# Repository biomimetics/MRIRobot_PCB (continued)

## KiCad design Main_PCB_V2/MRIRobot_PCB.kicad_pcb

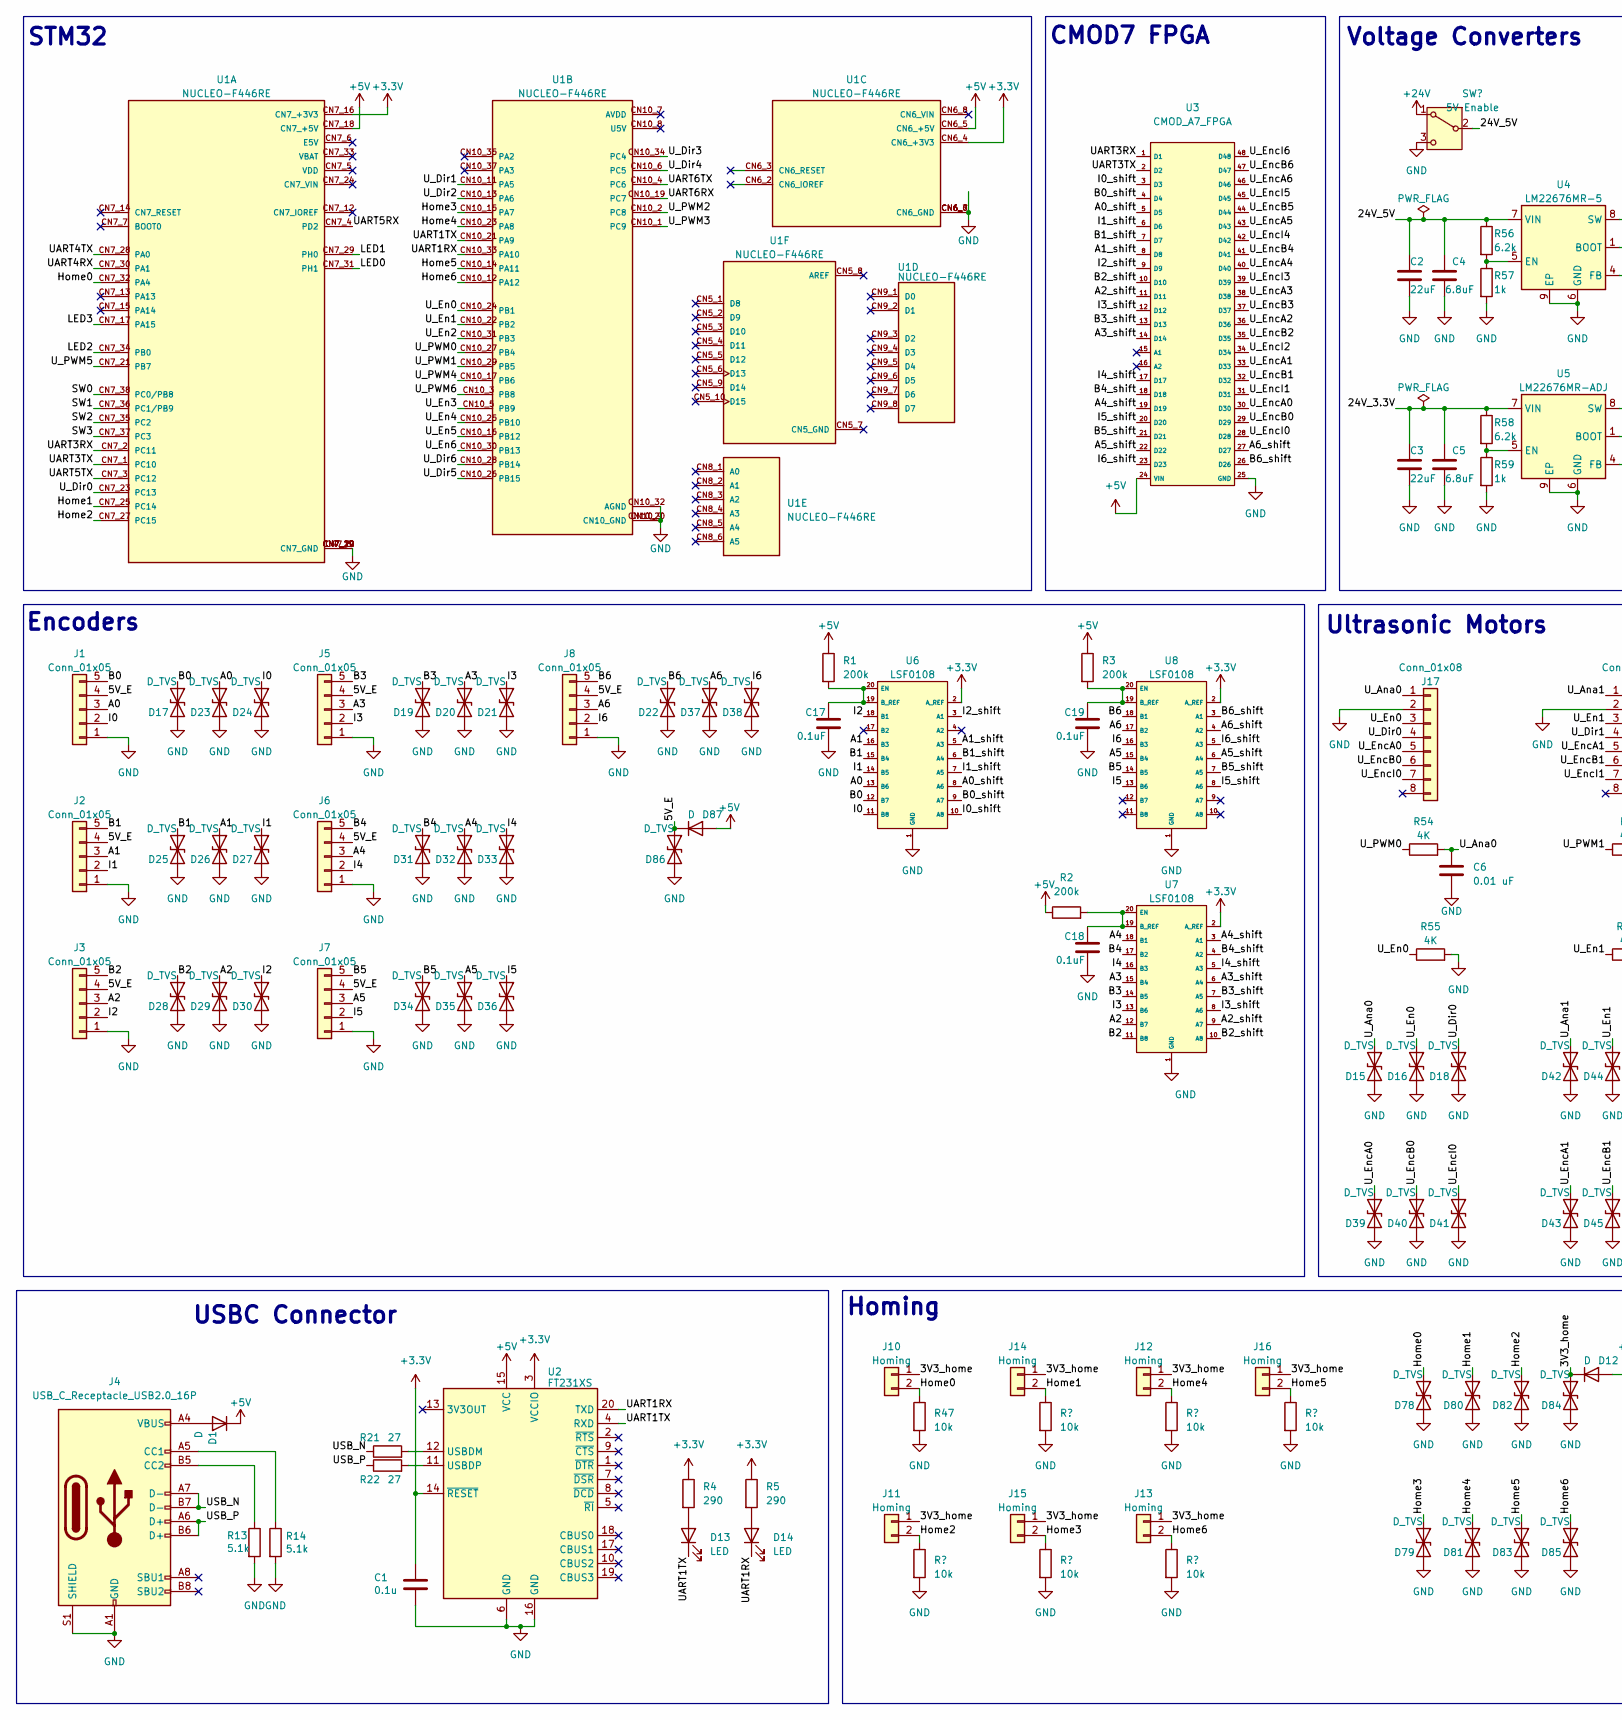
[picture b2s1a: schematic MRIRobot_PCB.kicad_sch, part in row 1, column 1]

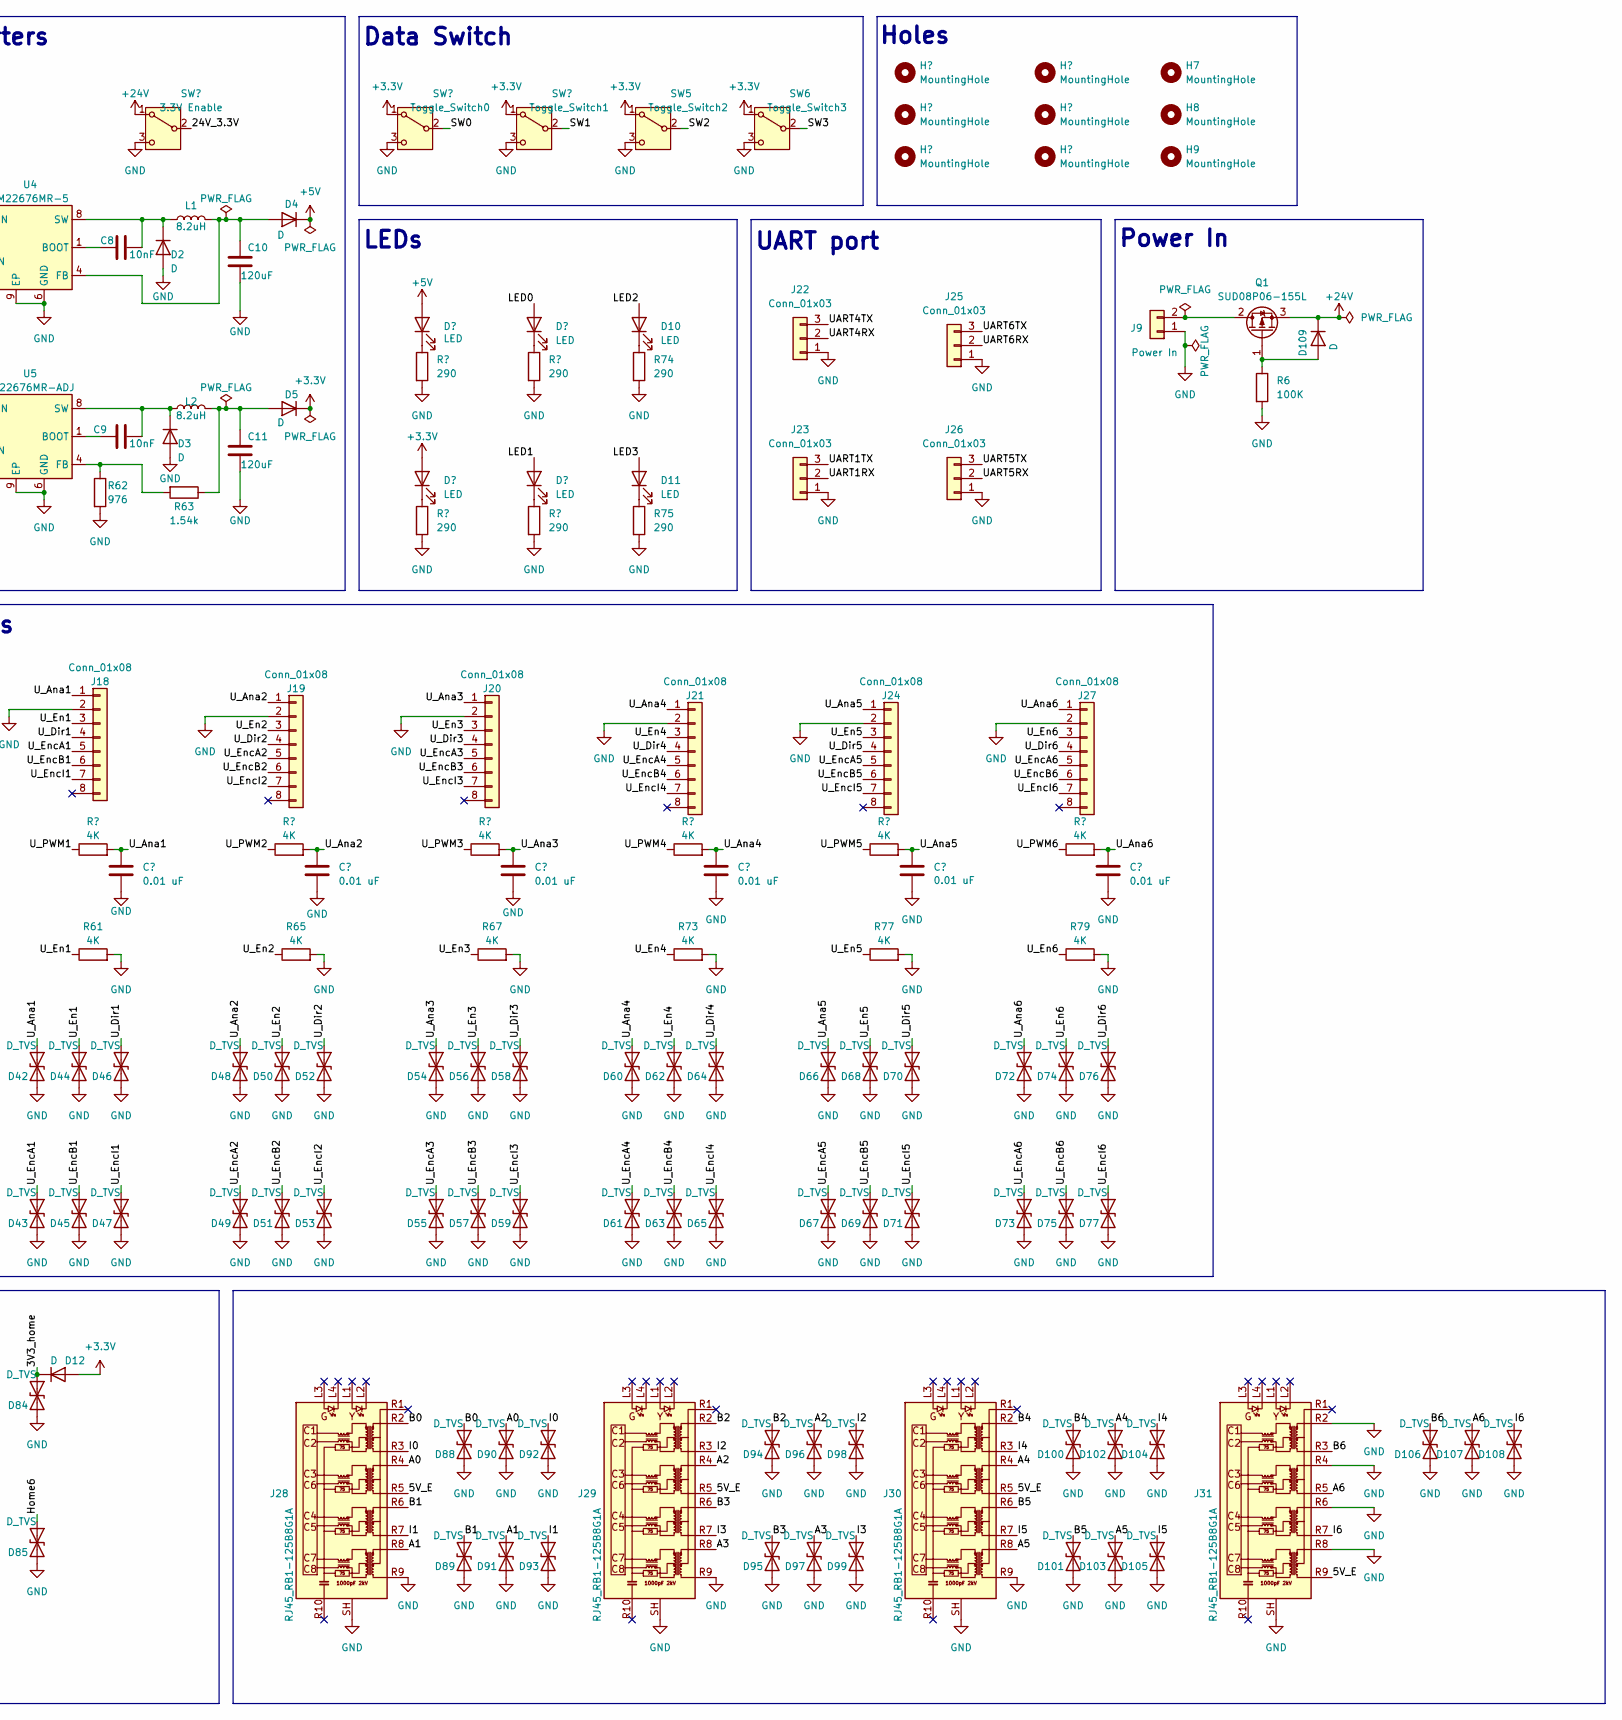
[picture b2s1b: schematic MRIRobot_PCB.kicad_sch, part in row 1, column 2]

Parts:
C1: 0.1u; C_0603_1608Metric_Pad1.08x0.95mm_HandSolder
C2, C3: 22uF; CP_Radial_D5.0mm_P2.00mm
C4, C5: 6.8uF; C_0805_2012Metric
C6, C7, C12, C13, C14, C15, C16: 0.01 uF; C_0805_2012Metric_Pad1.18x1.45mm_HandSolder
C8, C9: 10nF; C_0805_2012Metric
C10, C11: 120uF; CP_Radial_D6.3mm_P2.50mm
C17, C18, C19: 0.1uF; C_0805_2012Metric_Pad1.18x1.45mm_HandSolder
D1, D2, D3, D4, D5, D109: D; D_SMA_Handsoldering
D6, D7, D8, D9, D10, D11, D13, D14: LED; LED_0805_2012Metric_Pad1.15x1.40mm_HandSolder
D12, D87: D; D_SOD-128
D15, D16, D17, D18, D19, D20, D21, D22, D23, D24, D25, D26, D27, D28, D29, D30, D31, D32, D33, D34, D35, D36, D37, D38, D39, D40, D41, D42, D43, D44, D45, D46, D47, D48, D49, D50, D51, D52, D53, D54, D55, D56, D57, D58, D59, D60, D61, D62, D63, D64, D65, D66, D67, D68, D69, D70, D71, D72, D73, D74, D75, D76, D77, D78, D79, D80, D81, D82, D83, D84, D85, D86, D88, D89, D90, D91, D92, D93, D94, D95, D96, D97, D98, D99, D100, D101, D102, D103, D104, D105, D106, D107, D108: D_TVS; D_SOD-123F
H1, H2, H3, H4, H5, H6, H7, H8, H9: MountingHole; MountingHole_3.2mm_M3
J1, J2, J3, J5, J6, J7, J8: Conn_01x05; JST_EH_B5B-EH-A_1x05_P2.50mm_Vertical
J4: USB_C_Receptacle_USB2.0_16P; USB_C_Receptacle_GCT_USB4105-xx-A_16P_TopMnt_Horizontal
J9: Power In; AMASS_XT60-M_1x02_P7.20mm_Vertical
J10, J11, J12, J13, J14, J15, J16: Homing; JST_EH_B2B-EH-A_1x02_P2.50mm_Vertical
J17, J18, J19, J20, J21, J24, J27: Conn_01x08; JST_EH_B8B-EH-A_1x08_P2.50mm_Vertical
J22, J23, J25, J26: Conn_01x03; JST_XA_B03B-XASK-1-A_1x03_P2.50mm_Vertical
J28, J29, J30, J31: RJ45_RB1-125B8G1A; RJ45_UDE_RB1-125B8G1A
L1, L2: 8.2uH; L_7.3x7.3_H3.5
Q1: SUD08P06-155L; TO-252-2
R1, R2, R3: 200k; C_0805_2012Metric_Pad1.18x1.45mm_HandSolder
R4, R5, R68, R69, R70, R71, R74, R75: 290; C_0805_2012Metric_Pad1.18x1.45mm_HandSolder
R6: 100K; R_0805_2012Metric
R13, R14: 5.1k; R_0603_1608Metric_Pad0.98x0.95mm_HandSolder
R21, R22: 27; R_0603_1608Metric_Pad0.98x0.95mm_HandSolder
R47, R48, R49, R50, R51, R52, R53: 10k; C_0805_2012Metric_Pad1.18x1.45mm_HandSolder
R54, R55, R60, R61, R64, R65, R66, R67, R72, R73, R76, R77, R78, R79: 4K; C_0805_2012Metric_Pad1.18x1.45mm_HandSolder
R56, R58: 6.2k; R_0805_2012Metric
R57, R59: 1k; R_0805_2012Metric
R62: 976; R_0805_2012Metric
R63: 1.54k; R_0805_2012Metric
SW1: 5V Enable; SW_Slide_SPDT_Straight_CK_OS102011MS2Q
SW2: 3.3V Enable; SW_Slide_SPDT_Straight_CK_OS102011MS2Q
SW3: Toggle_Switch0; SW_Slide_SPDT_Straight_CK_OS102011MS2Q
SW4: Toggle_Switch1; SW_Slide_SPDT_Straight_CK_OS102011MS2Q
SW5: Toggle_Switch2; SW_Slide_SPDT_Straight_CK_OS102011MS2Q
SW6: Toggle_Switch3; SW_Slide_SPDT_Straight_CK_OS102011MS2Q
U1: NUCLEO-F446RE; MODULE_NUCLEO-F446RE; PARTREV 13
U2: FT231XS; SSOP-20_3.9x8.7mm_P0.635mm
U3: CMOD_A7_FPGA; CMODA7
U4: LM22676MR-5; TI_SO-PowerPAD-8
U5: LM22676MR-ADJ; TI_SO-PowerPAD-8
U6, U7, U8: LSF0108; TSSOP-20_4.4x6.5mm_P0.65mm

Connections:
+3.3V: C1.1, D5.1 (K), D7.2 (A), D12.2 (A), R4.1, R5.1, SW3.1 (A), SW4.1 (A), SW5.1 (A), SW6.1 (A), U1.CN6_4 (CN6_+3V3), U1.CN7_16 (CN7_+3V3), U2.3 (VCCIO), U2.14 (~RESET), U6.2 (A_REF), U7.2 (A_REF), U8.2 (A_REF)
+5V: D1.1 (K), D4.1 (K), D6.2 (A), D87.2 (A), R1.1, R2.1, R3.1, U1.CN6_5 (CN6_+5V), U1.CN7_18 (CN7_+5V), U2.15 (VCC), U3.24 (VIN)
+24V: D109.1 (K), Q1.3 (S), SW1.1 (A), SW2.1 (A)
/3V3_home: D12.1 (K), D84.1 (A1), J10.1, J11.1, J12.1, J13.1, J14.1, J15.1, J16.1
/5V_E: D86.1 (A1), D87.1 (K), J1.4, J2.4, J3.4, J5.4, J6.4, J7.4, J8.4, J28.R5 (TD2-), J29.R5 (TD2-), J30.R5 (TD2-), J31.R9 (TD4-)
/24V_3.3V: C3.1, C5.1, R58.1, SW2.2 (B), U5.7 (VIN)
/24V_5V: C2.1, C4.1, R56.1, SW1.2 (B), U4.7 (VIN)
/A0: D23.1 (A1), D90.1 (A1), J1.3, J28.R4 (TD2+), U6.13 (B6)
/A0_shift: U3.5 (D5), U6.8 (A6)
/A1: D26.1 (A1), D91.1 (A1), J2.3, J28.R8 (TD4+), U6.16 (B3)
/A1_shift: U3.8 (D8), U6.5 (A3)
/A2: D29.1 (A1), D96.1 (A1), J3.3, J29.R4 (TD2+), U7.12 (B7)
/A2_shift: U3.11 (D11), U7.9 (A7)
/A3: D20.1 (A1), D97.1 (A1), J5.3, J29.R8 (TD4+), U7.15 (B4)
/A3_shift: U3.14 (D14), U7.6 (A4)
/A4: D32.1 (A1), D102.1 (A1), J6.3, J30.R4 (TD2+), U7.18 (B1)
/A4_shift: U3.19 (D19), U7.3 (A1)
/A5: D35.1 (A1), D103.1 (A1), J7.3, J30.R8 (TD4+), U8.15 (B4)
/A5_shift: U3.22 (D22), U8.6 (A4)
/A6: D37.1 (A1), D107.1 (A1), J8.3, J31.R5 (TD2-), U8.17 (B2)
/A6_shift: U3.27 (D27), U8.4 (A2)
/B0: D17.1 (A1), D88.1 (A1), J1.5, J28.R2 (TD1+), U6.12 (B7)
/B0_shift: U3.4 (D4), U6.9 (A7)
/B1: D25.1 (A1), D89.1 (A1), J2.5, J28.R6 (TD3+), U6.15 (B4)
/B1_shift: U3.7 (D7), U6.6 (A4)
/B2: D28.1 (A1), D94.1 (A1), J3.5, J29.R2 (TD1+), U7.11 (B8)
/B2_shift: U3.10 (D10), U7.10 (A8)
/B3: D19.1 (A1), D95.1 (A1), J5.5, J29.R6 (TD3+), U7.14 (B5)
/B3_shift: U3.13 (D13), U7.7 (A5)
/B4: D31.1 (A1), D100.1 (A1), J6.5, J30.R2 (TD1+), U7.17 (B2)
/B4_shift: U3.18 (D18), U7.4 (A2)
/B5: D34.1 (A1), D101.1 (A1), J7.5, J30.R6 (TD3+), U8.14 (B5)
/B5_shift: U3.21 (D21), U8.7 (A5)
/B6: D22.1 (A1), D106.1 (A1), J8.5, J31.R3 (TD1-), U8.18 (B1)
/B6_shift: U3.26 (D26), U8.3 (A1)
/Home0: D78.1 (A1), J10.2, R47.1, U1.CN7_32 (PA4)
/Home1: D80.1 (A1), J14.2, R51.1, U1.CN7_25 (PC14)
/Home2: D82.1 (A1), J11.2, R48.1, U1.CN7_27 (PC15)
/Home3: D79.1 (A1), J15.2, R52.1, U1.CN10_15 (PA7)
/Home4: D81.1 (A1), J12.2, R49.1, U1.CN10_23 (PA8)
/Home5: D83.1 (A1), J16.2, R53.1, U1.CN10_14 (PA11)
/Home6: D85.1 (A1), J13.2, R50.1, U1.CN10_12 (PA12)
/I0: D24.1 (A1), D92.1 (A1), J1.2, J28.R3 (TD1-), U6.11 (B8)
/I0_shift: U3.3 (D3), U6.10 (A8)
/I1: D27.1 (A1), D93.1 (A1), J2.2, J28.R7 (TD3-), U6.14 (B5)
/I1_shift: U3.6 (D6), U6.7 (A5)
/I2: D30.1 (A1), D98.1 (A1), J3.2, J29.R3 (TD1-), U6.18 (B1)
/I2_shift: U3.9 (D9), U6.3 (A1)
/I3: D21.1 (A1), D99.1 (A1), J5.2, J29.R7 (TD3-), U7.13 (B6)
/I3_shift: U3.12 (D12), U7.8 (A6)
/I4: D33.1 (A1), D104.1 (A1), J6.2, J30.R3 (TD1-), U7.16 (B3)
/I4_shift: U3.17 (D17), U7.5 (A3)
/I5: D36.1 (A1), D105.1 (A1), J7.2, J30.R7 (TD3-), U8.13 (B6)
/I5_shift: U3.20 (D20), U8.8 (A6)
/I6: D38.1 (A1), D108.1 (A1), J8.2, J31.R7 (TD3-), U8.16 (B3)
/I6_shift: U3.23 (D23), U8.5 (A3)
/LED0: D8.2 (A), U1.CN7_31 (PH1)
/LED1: D9.2 (A), U1.CN7_29 (PH0)
/LED2: D10.2 (A), U1.CN7_34 (PB0)
/LED3: D11.2 (A), U1.CN7_17 (PA15)
/SW0: SW3.2 (B), U1.CN7_38 (PC0/PB8)
/SW1: SW4.2 (B), U1.CN7_36 (PC1/PB9)
/SW2: SW5.2 (B), U1.CN7_35 (PC2)
/SW3: SW6.2 (B), U1.CN7_37 (PC3)
/UART1RX: D14.1 (K), J23.2, U1.CN10_33 (PA10), U2.20 (TXD)
/UART1TX: D13.1 (K), J23.3, U1.CN10_21 (PA9), U2.4 (RXD)
/UART3RX: U1.CN7_2 (PC11), U3.1 (D1)
/UART3TX: U1.CN7_1 (PC10), U3.2 (D2)
/UART4RX: J22.2, U1.CN7_30 (PA1)
/UART4TX: J22.3, U1.CN7_28 (PA0)
/UART5RX: J26.2, U1.CN7_4 (PD2)
/UART5TX: J26.3, U1.CN7_3 (PC12)
/UART6RX: J25.2, U1.CN10_19 (PC7)
/UART6TX: J25.3, U1.CN10_4 (PC6)
/USB_N: J4.A7 (D-), J4.B7 (D-), R21.1
/USB_P: J4.A6 (D+), J4.B6 (D+), R22.1
/U_Ana0: C6.1, D15.1 (A1), J17.1, R54.2
/U_Ana1: C7.1, D42.1 (A1), J18.1, R60.2
/U_Ana2: C12.1, D48.1 (A1), J19.1, R64.2
/U_Ana3: C13.1, D54.1 (A1), J20.1, R66.2
/U_Ana4: C14.1, D60.1 (A1), J21.1, R72.2
/U_Ana5: C15.1, D66.1 (A1), J24.1, R76.2
/U_Ana6: C16.1, D72.1 (A1), J27.1, R78.2
/U_Dir0: D18.1 (A1), J17.4, U1.CN7_23 (PC13)
/U_Dir1: D46.1 (A1), J18.4, U1.CN10_11 (PA5)
/U_Dir2: D52.1 (A1), J19.4, U1.CN10_13 (PA6)
/U_Dir3: D58.1 (A1), J20.4, U1.CN10_34 (PC4)
/U_Dir4: D64.1 (A1), J21.4, U1.CN10_6 (PC5)
/U_Dir5: D70.1 (A1), J24.4, U1.CN10_26 (PB15)
/U_Dir6: D76.1 (A1), J27.4, U1.CN10_28 (PB14)
/U_En0: D16.1 (A1), J17.3, R55.1, U1.CN10_24 (PB1)
/U_En1: D44.1 (A1), J18.3, R61.1, U1.CN10_22 (PB2)
/U_En2: D50.1 (A1), J19.3, R65.1, U1.CN10_31 (PB3)
/U_En3: D56.1 (A1), J20.3, R67.1, U1.CN10_5 (PB9)
/U_En4: D62.1 (A1), J21.3, R73.1, U1.CN10_25 (PB10)
/U_En5: D68.1 (A1), J24.3, R77.1, U1.CN10_16 (PB12)
/U_En6: D74.1 (A1), J27.3, R79.1, U1.CN10_30 (PB13)
/U_EncA0: D39.1 (A1), J17.5, U3.30 (D30)
/U_EncA1: D43.1 (A1), J18.5, U3.33 (D33)
/U_EncA2: D49.1 (A1), J19.5, U3.36 (D36)
/U_EncA3: D55.1 (A1), J20.5, U3.38 (D38)
/U_EncA4: D61.1 (A1), J21.5, U3.40 (D40)
/U_EncA5: D67.1 (A1), J24.5, U3.43 (D43)
/U_EncA6: D73.1 (A1), J27.5, U3.46 (D46)
/U_EncB0: D40.1 (A1), J17.6, U3.29 (D29)
/U_EncB1: D45.1 (A1), J18.6, U3.32 (D32)
/U_EncB2: D51.1 (A1), J19.6, U3.35 (D35)
/U_EncB3: D57.1 (A1), J20.6, U3.37 (D37)
/U_EncB4: D63.1 (A1), J21.6, U3.41 (D41)
/U_EncB5: D69.1 (A1), J24.6, U3.44 (D44)
/U_EncB6: D75.1 (A1), J27.6, U3.47 (D47)
/U_EncI0: D41.1 (A1), J17.7, U3.28 (D28)
/U_EncI1: D47.1 (A1), J18.7, U3.31 (D31)
/U_EncI2: D53.1 (A1), J19.7, U3.34 (D34)
/U_EncI3: D59.1 (A1), J20.7, U3.39 (D39)
/U_EncI4: D65.1 (A1), J21.7, U3.42 (D42)
/U_EncI5: D71.1 (A1), J24.7, U3.45 (D45)
/U_EncI6: D77.1 (A1), J27.7, U3.48 (D48)
/U_PWM0: R54.1, U1.CN10_27 (PB4)
/U_PWM1: R60.1, U1.CN10_29 (PB5)
/U_PWM2: R64.1, U1.CN10_2 (PC8)
/U_PWM3: R66.1, U1.CN10_1 (PC9)
/U_PWM4: R72.1, U1.CN10_17 (PB6)
/U_PWM5: R76.1, U1.CN7_21 (PB7)
/U_PWM6: R78.1, U1.CN10_3 (PB8)
GND: C1.2, C2.2, C3.2, C4.2, C5.2, C6.2, C7.2, C10.2, C11.2, C12.2, C13.2, C14.2, C15.2, C16.2, C17.2, C18.2, C19.2, D2.2 (A), D3.2 (A), D15.2 (A2), D16.2 (A2), D17.2 (A2), D18.2 (A2), D19.2 (A2), D20.2 (A2), D21.2 (A2), D22.2 (A2), D23.2 (A2), D24.2 (A2), D25.2 (A2), D26.2 (A2), D27.2 (A2), D28.2 (A2), D29.2 (A2), D30.2 (A2), D31.2 (A2), D32.2 (A2), D33.2 (A2), D34.2 (A2), D35.2 (A2), D36.2 (A2), D37.2 (A2), D38.2 (A2), D39.2 (A2), D40.2 (A2), D41.2 (A2), D42.2 (A2), D43.2 (A2), D44.2 (A2), D45.2 (A2), D46.2 (A2), D47.2 (A2), D48.2 (A2), D49.2 (A2), D50.2 (A2), D51.2 (A2), D52.2 (A2), D53.2 (A2), D54.2 (A2), D55.2 (A2), D56.2 (A2), D57.2 (A2), D58.2 (A2), D59.2 (A2), D60.2 (A2), D61.2 (A2), D62.2 (A2), D63.2 (A2), D64.2 (A2), D65.2 (A2), D66.2 (A2), D67.2 (A2), D68.2 (A2), D69.2 (A2), D70.2 (A2), D71.2 (A2), D72.2 (A2), D73.2 (A2), D74.2 (A2), D75.2 (A2), D76.2 (A2), D77.2 (A2), D78.2 (A2), D79.2 (A2), D80.2 (A2), D81.2 (A2), D82.2 (A2), D83.2 (A2), D84.2 (A2), D85.2 (A2), D86.2 (A2), D88.2 (A2), D89.2 (A2), D90.2 (A2), D91.2 (A2), D92.2 (A2), D93.2 (A2), D94.2 (A2), D95.2 (A2), D96.2 (A2), D97.2 (A2), D98.2 (A2), D99.2 (A2), D100.2 (A2), D101.2 (A2), D102.2 (A2), D103.2 (A2), D104.2 (A2), D105.2 (A2), D106.2 (A2), D107.2 (A2), D108.2 (A2), J1.1, J2.1, J3.1, J4.A1 (GND), J4.A12 (GND), J4.B1 (GND), J4.B12 (GND), J4.S1 (SHIELD), J5.1, J6.1, J7.1, J8.1, J9.1, J17.2, J18.2, J19.2, J20.2, J21.2, J22.1, J23.1, J24.2, J25.1, J26.1, J27.2, J28.R9 (TD4-), J28.SH, J29.R9 (TD4-), J29.SH, J30.R9 (TD4-), J30.SH, J31.R2 (TD1+), J31.R4 (TD2+), J31.R6 (TD3+), J31.R8 (TD4+), J31.SH, R6.2, R13.2, R14.2, R47.2, R48.2, R49.2, R50.2, R51.2, R52.2, R53.2, R55.2, R57.2, R59.2, R61.2, R62.2, R65.2, R67.2, R68.2, R69.2, R70.2, R71.2, R73.2, R74.2, R75.2, R77.2, R79.2, SW1.3 (C), SW2.3 (C), SW3.3 (C), SW4.3 (C), SW5.3 (C), SW6.3 (C), U1.CN6_6 (CN6_GND), U1.CN6_7 (CN6_GND), U1.CN7_8 (CN7_GND), U1.CN7_19 (CN7_GND), U1.CN7_20 (CN7_GND), U1.CN7_22 (CN7_GND), U1.CN10_9 (CN10_GND), U1.CN10_20 (CN10_GND), U1.CN10_32 (AGND), U2.6 (GND), U2.16 (GND), U3.25 (GND), U4.6 (GND), U4.9 (EP), U5.6 (GND), U5.9 (EP), U6.1 (GND), U7.1 (GND), U8.1 (GND)
unnamed: D1.2 (A), J4.A4 (VBUS), J4.A9 (VBUS), J4.B4 (VBUS), J4.B9 (VBUS)
unnamed: C8.2, D2.1 (K), L1.1, U4.8 (SW)
unnamed: C9.2, D3.1 (K), L2.1, U5.8 (SW)
unnamed: C10.1, D4.2 (A), L1.2, U4.4 (FB)
unnamed: C11.1, D5.2 (A), L2.2, R63.1
unnamed: D6.1 (K), R68.1
unnamed: D7.1 (K), R69.1
unnamed: D8.1 (K), R70.1
unnamed: D9.1 (K), R71.1
unnamed: D10.1 (K), R74.1
unnamed: D11.1 (K), R75.1
unnamed: D13.2 (A), R4.2
unnamed: D14.2 (A), R5.2
unnamed: D109.2 (A), Q1.1 (G), R6.1
unnamed: J4.A5 (CC1), R14.1
unnamed: J4.B5 (CC2), R13.1
unnamed: J9.2, Q1.2 (D)
unnamed: R21.2, U2.12 (USBDM)
unnamed: R22.2, U2.11 (USBDP)
unnamed: C8.1, U4.1 (BOOT)
unnamed: R56.2, R57.1, U4.5 (EN)
unnamed: C9.1, U5.1 (BOOT)
unnamed: R58.2, R59.1, U5.5 (EN)
unnamed: R62.1, R63.2, U5.4 (FB)
unnamed: C17.1, R1.2, U6.19 (B_REF), U6.20 (EN)
unnamed: C18.1, R2.2, U7.19 (B_REF), U7.20 (EN)
unnamed: C19.1, R3.2, U8.19 (B_REF), U8.20 (EN)

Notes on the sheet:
Holes
STM32
LEDs
Data Switch
Ultrasonic Motors
Homing
USBC Connector
CMOD7 FPGA
Power In
UART port
Encoders
Voltage Converters

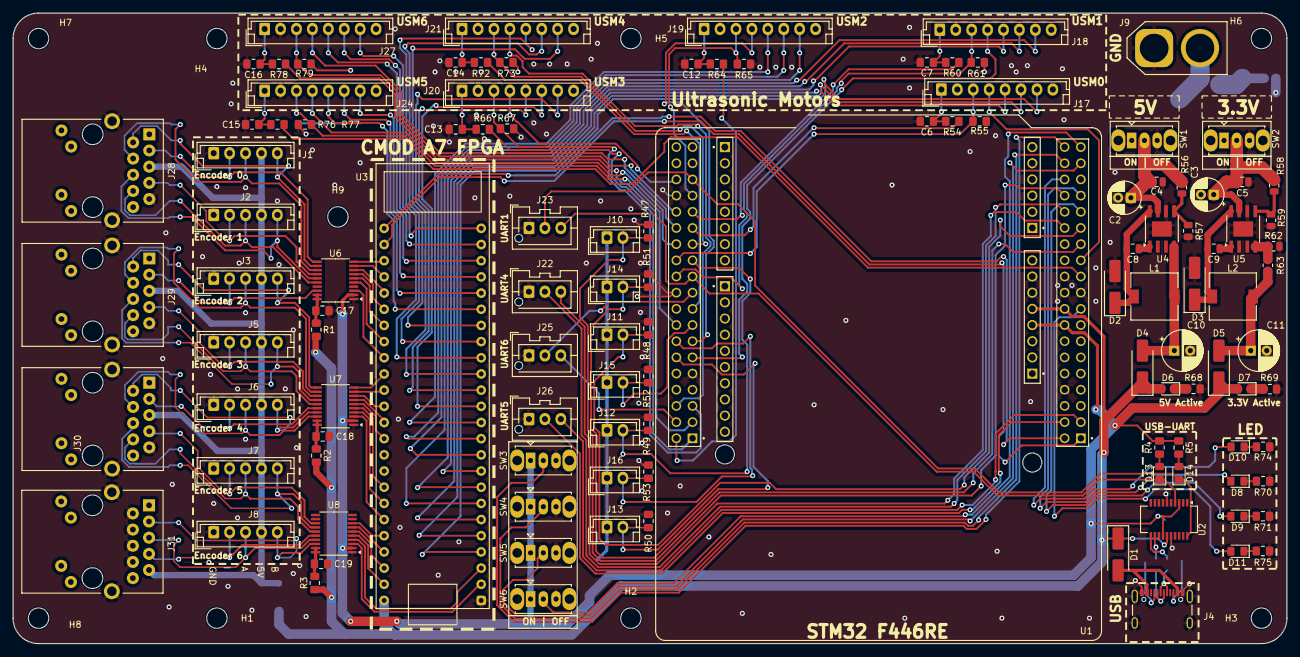
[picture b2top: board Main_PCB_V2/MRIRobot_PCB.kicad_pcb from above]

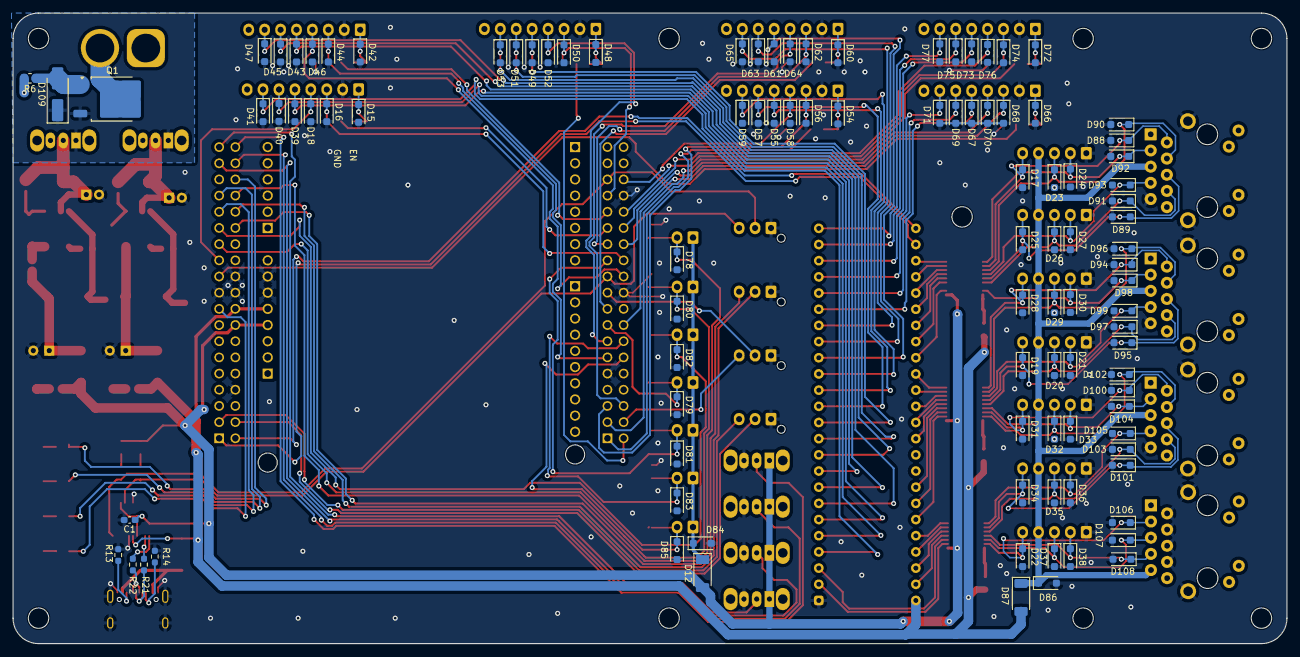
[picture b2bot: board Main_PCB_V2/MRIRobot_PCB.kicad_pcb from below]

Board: 2 copper layers, 200.0 x 99.0 mm, 228 parts (103 on the bottom side), 153 nets.

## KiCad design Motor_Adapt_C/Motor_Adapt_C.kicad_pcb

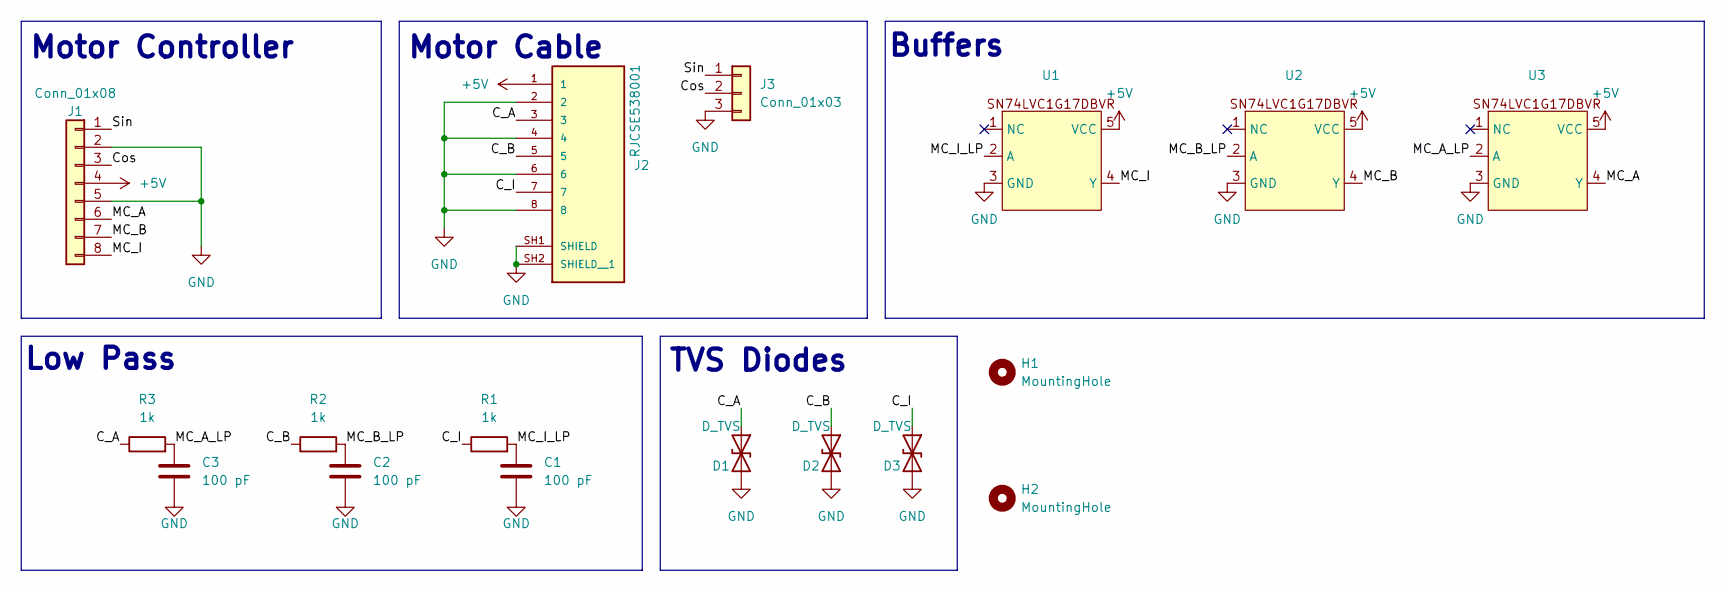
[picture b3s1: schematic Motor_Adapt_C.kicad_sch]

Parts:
C1, C2, C3: 100 pF; C_0805_2012Metric_Pad1.18x1.45mm_HandSolder
D1, D2, D3: D_TVS; D_SOD-123F
H1, H2: MountingHole; MountingHole_3.2mm_M3
J1: Conn_01x08; JST_EH_B8B-EH-A_1x08_P2.50mm_Vertical
J2: RJCSE538001; AMPHENOL_RJCSE538001; PARTREV A
J3: Conn_01x03; Molex_KK-396_A-41792-0003_1x03_P3.96mm_Horizontal
R1, R2, R3: 1k; C_0805_2012Metric_Pad1.18x1.45mm_HandSolder
U1, U2, U3: SOT-23-5

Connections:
+5V: J1.4, J2.1, U1.5 (VCC), U2.5 (VCC), U3.5 (VCC)
/C_A: D1.1 (A1), J2.3, R3.1
/C_B: D2.1 (A1), J2.5, R2.1
/C_I: D3.1 (A1), J2.7, R1.1
/Cos: J1.3, J3.2
/MC_A: J1.6, U3.4 (Y)
/MC_A_LP: C3.1, R3.2, U3.2 (A)
/MC_B: J1.7, U2.4 (Y)
/MC_B_LP: C2.1, R2.2, U2.2 (A)
/MC_I: J1.8, U1.4 (Y)
/MC_I_LP: C1.1, R1.2, U1.2 (A)
/Sin: J1.1, J3.1
GND: C1.2, C2.2, C3.2, D1.2 (A2), D2.2 (A2), D3.2 (A2), J1.2, J1.5, J2.2, J2.4, J2.6, J2.8, J2.SH1 (SHIELD), J2.SH2 (SHIELD__1), J3.3, U1.3 (GND), U2.3 (GND), U3.3 (GND)

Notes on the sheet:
Low Pass
TVS Diodes
Buffers
Motor Cable
Motor Controller

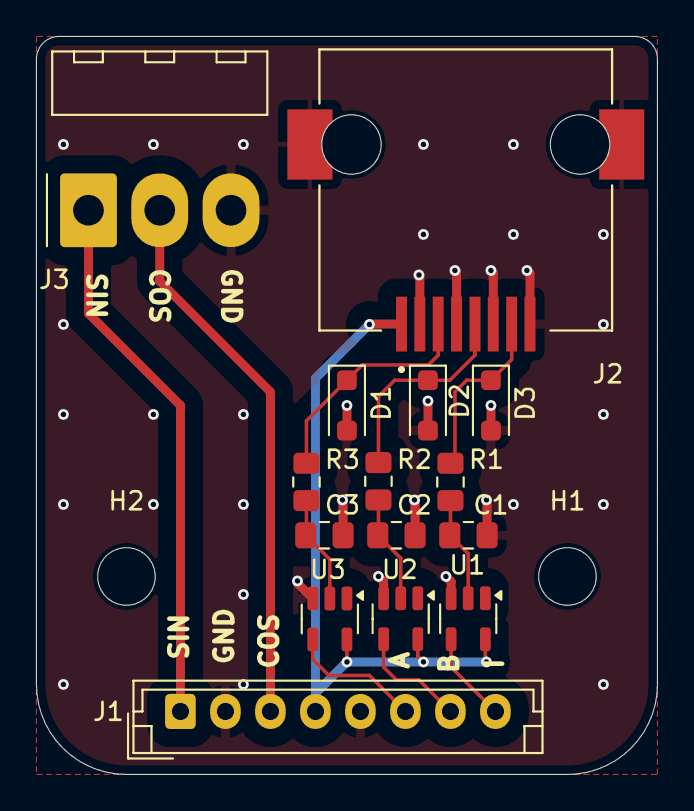
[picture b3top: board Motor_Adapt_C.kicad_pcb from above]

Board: 2 copper layers, 34.5 x 41.0 mm, 17 parts (0 on the bottom side), 13 nets.

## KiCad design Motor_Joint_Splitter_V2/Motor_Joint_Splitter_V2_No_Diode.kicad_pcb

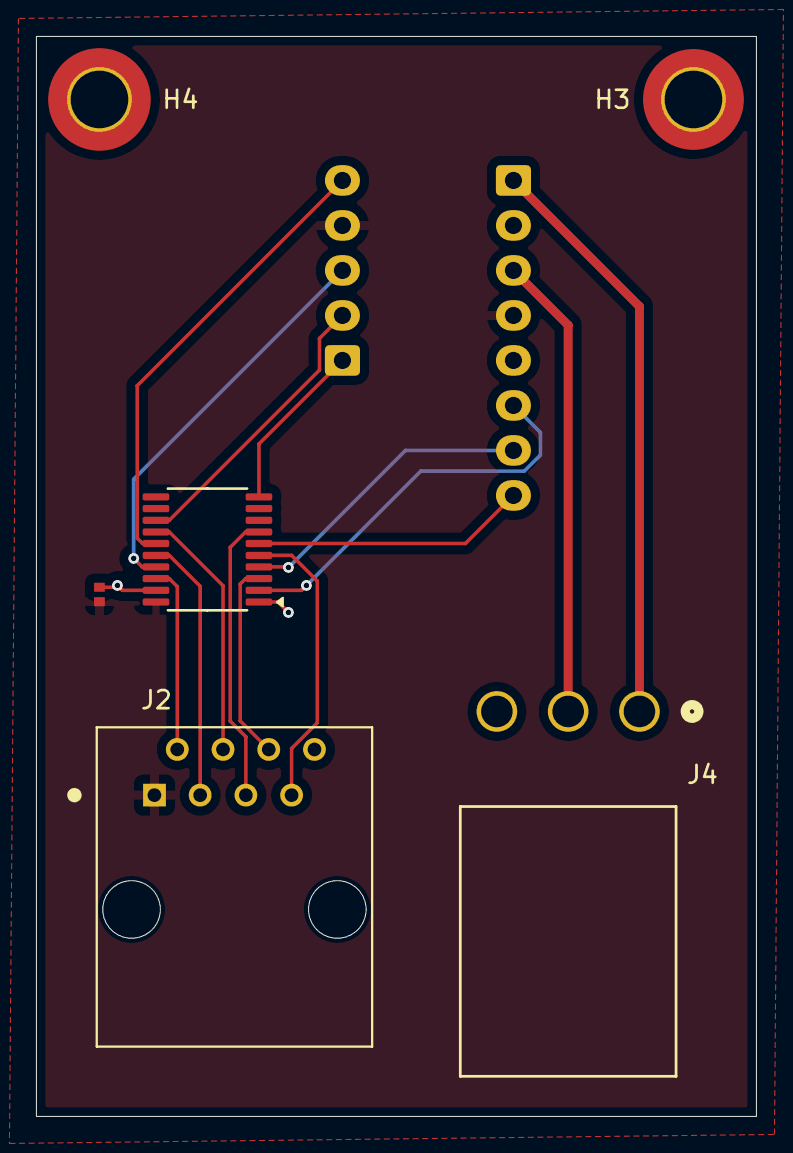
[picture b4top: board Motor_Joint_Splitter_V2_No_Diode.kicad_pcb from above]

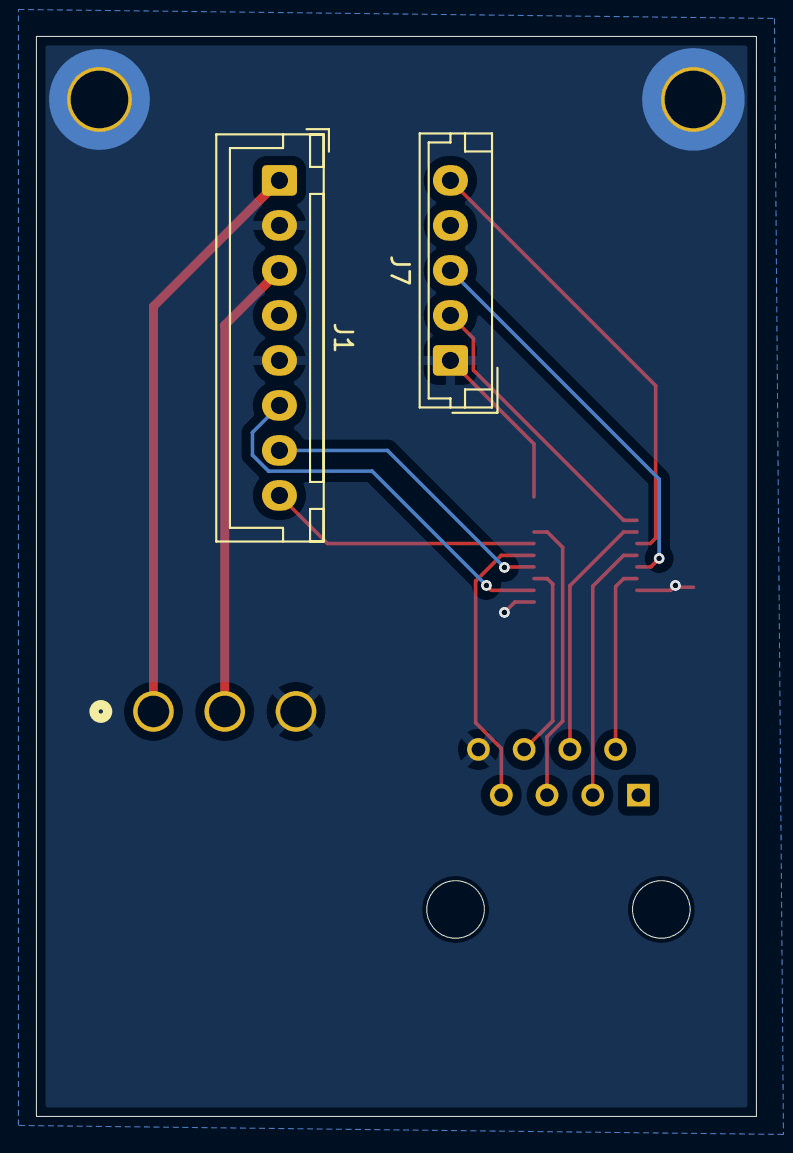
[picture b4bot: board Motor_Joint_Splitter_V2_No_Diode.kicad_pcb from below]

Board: 2 copper layers, 40.0 x 60.0 mm, 8 parts (2 on the bottom side), 16 nets.

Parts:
D1: H5VL10B; D_DFN1006-2L
H3: MountingHole_Pad; MountingHole_3.2mm_M3_DIN965_Pad_TopBottom
H4: MountingHole_Pad; MountingHole_3.2mm_M3_ISO7380_Pad_TopBottom
J1: Conn_01x08; JST_XH_B8B-XH-A_1x08_P2.50mm_Vertical
J2: 54602-908LF; AMPHENOL_54602-908LF
J4: 26605030; CONN_SDA-41792_M450_03_MOL
J7: Conn_01x05; JST_EH_B5B-EH-A_1x05_P2.50mm_Vertical
U1: 74AHCT244; TSSOP-20_4.4x6.5mm_P0.65mm

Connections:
+5V: D1.1, J1.4, J2.1, J7.4, U1.20 (VCC)
/C_A: J1.6, U1.2 (1A0)
/C_A_Out: J2.2, U1.18 (1Y0)
/C_B: J1.7, U1.4 (1A1)
/C_B_Out: J2.3, U1.16 (1Y1)
/C_I: J1.8, U1.6 (1A2)
/C_I_Out: J2.4, U1.14 (1Y2)
/Cos: J1.3, J4.2
/SEA_A: J7.3, U1.17 (2A0)
/SEA_A_Out: J2.6, U1.3 (2Y0)
/SEA_B: J7.5, U1.15 (2A1)
/SEA_B_Out: J2.7, U1.5 (2Y1)
/SEA_I: J7.2, U1.13 (2A2)
/SEA_I_Out: J2.5, U1.7 (2Y2)
/Sin: J1.1, J4.1
GND: D1.2, H3.1, H4.1, J1.2, J1.5, J2.8, J4.3, J7.1, U1.1 (1OE), U1.10 (GND), U1.19 (2OE)

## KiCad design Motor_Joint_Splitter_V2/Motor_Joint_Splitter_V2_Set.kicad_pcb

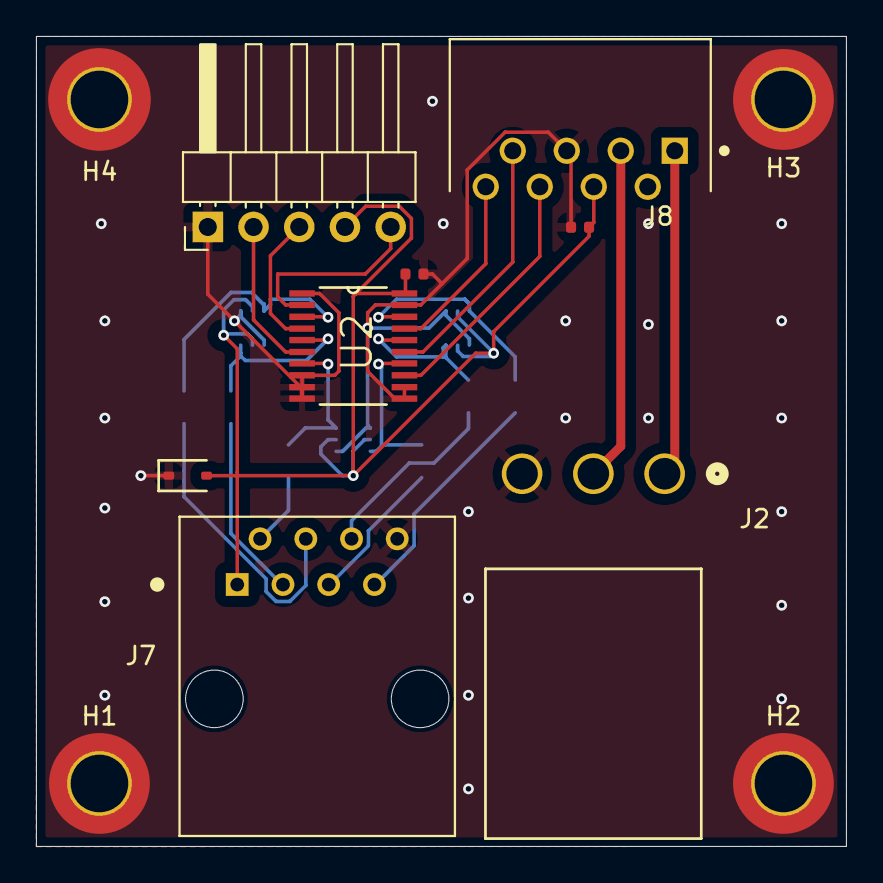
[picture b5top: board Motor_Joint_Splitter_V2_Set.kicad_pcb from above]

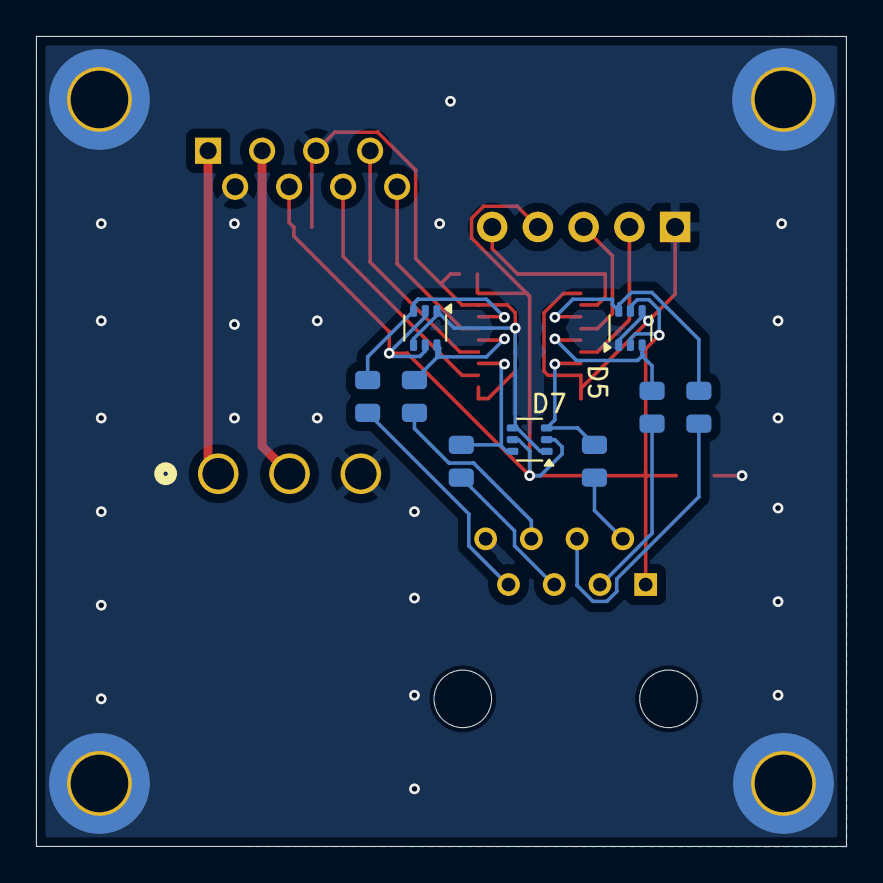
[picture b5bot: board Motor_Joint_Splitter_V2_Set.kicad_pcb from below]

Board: 2 copper layers, 45.0 x 45.0 mm, 21 parts (9 on the bottom side), 22 nets.

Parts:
C1, C2: 1uF; C_0402
D4: H5VHD3BC; D_SOD-323
D5, D6, D7: BAT54SDW; SOT-363_SC-70-6
H1, H2, H3: MountingHole_Pad; MountingHole_3.2mm_M3_DIN965_Pad_TopBottom
H4: MountingHole_Pad; MountingHole_3.2mm_M3_ISO7380_Pad_TopBottom
J2: 26605030; CONN_SDA-41792_M450_03_MOL
J7: ethernet_54602-908LF; AMPHENOL_54602-908LF
J8: motor_connector_292206-8; TE_292206-8
J9: Conn_01x05; PinHeader_1x05_P2.54mm_Horizontal
R13, R14, R15, R16, R17, R19: 120Ω; R_0805
U2: 74ACT244MTCX; line_driver_SOP65P640X120-20N

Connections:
+5V: C1.2, C2.1, D4.2, D5.2 (K), D5.5 (K), D6.2 (K), D6.5 (K), D7.2 (K), D7.5 (K), J7.1, J8.4, J9.4, U2.20 (VCC)
/C_A: J8.6, U2.13 (I6)
/C_A_Out: D7.3 (A), R19.1, U2.7 (O6)
/C_A_Out_2: J7.2, R19.2
/C_B: J8.7, U2.15 (I5)
/C_B_Out: D5.3 (K), R13.1, U2.5 (O5)
/C_B_Out_2: J7.3, R13.2
/C_I: J8.8, U2.17 (I4)
/C_I_Out: D5.6 (K), R14.1, U2.3 (O4)
/C_I_Out_2: J7.4, R14.2
/Cos: J2.2, J8.3
/SEA_A: J9.3, U2.4 (I1)
/SEA_A_Out: D6.6 (K), R15.1, U2.16 (O1)
/SEA_A_Out_2: J7.6, R15.2
/SEA_B: J9.5, U2.2 (I0)
/SEA_B_Out: D6.3 (A), R16.1, U2.18 (O0)
/SEA_B_Out_2: J7.7, R16.2
/SEA_I: J9.2, U2.6 (I2)
/SEA_I_Out: D7.6 (A), R17.1, U2.14 (O2)
/SEA_I_Out_2: J7.5, R17.2
/Sin: J2.1, J8.1
GND: C1.1, C2.2, D4.1, D5.1 (A), D5.4 (A), D6.1 (A), D6.4 (A), D7.1 (A), D7.4 (A), H1.1, H2.1, H3.1, H4.1, J2.3, J7.8, J8.2, J8.5, J9.1, U2.1 (~OE1), U2.8 (I3), U2.9 (O7), U2.10 (GND), U2.11 (I7), U2.12 (O3), U2.19 (~OE2)

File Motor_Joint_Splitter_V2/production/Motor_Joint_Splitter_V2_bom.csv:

"Reference","Value","Datasheet","Footprint","Qty","DNP","LCSC"
"C1,C2","1uF","https://www.lcsc.com/datasheet/lcsc_datasheet_2304140030_Sam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","PCM_JLCPCB:C_0402","2","","C52923"
"D4","H5VHD3BC","https://wmsc.lcsc.com/wmsc/upload/file/pdf/v2/lcsc/240126152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","PCM_JLCPCB:D_SOD-323","1","","C20615804"
"D5,D6,D7","BAT54SDW","https://www.diodes.com/assets/Datasheets/BAT54TW_ADW_CDW_SDW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","Package_TO_SOT_SMD:SOT-363_SC-70-6","3","","C77323"
"J2","26605030","https://www.molex.com/en-us/products/part-detail-pdf/2660503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","splitter_parts:CONN_SDA-41792_M450_03_MOL","1","","C587093"
"J7","ethernet_54602-908LF","https://cdn.amphenol-cs.com/media/wysiwyg/files/documentatio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","splitter_parts:AMPHENOL_54602-908LF","1","","C2847314"
"J8","motor_connector_292206-8","","splitter_parts:TE_292206-8","1","","C591662"
"J9","Conn_01x05","~","Connector_PinHeader_2.54mm:PinHeader_1x05_P2.54mm_Horizontal","1","",""
"R13,R14,R15,R16,R17,R19","120Ω","https://www.lcsc.com/datasheet/lcsc_datasheet_2206010216_UNI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","PCM_JLCPCB:R_0805","6","","C17437"
"U2","74ACT244MTCX","","splitter_parts:line_driver_SOP65P640X120-20N","1","","C5496"
